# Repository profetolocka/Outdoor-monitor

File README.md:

[Go to English version](#english-version)

# Monitor ambiental de exterior

Consultá desde tu teléfono la temperatura, la humedad y la presión ambiental antes de salir de casa, con este práctico proyecto basado en un Atom Lite de M5Stack y la app ThingShow.

---

## 📂 Contenido

El repositorio está organizado en carpetas con el siguiente contenido:

**Code:** Código UIFlow2

**KiCad:** Proyecto de Kicad 9 con el esquemático y PCB

**images:** Imágenes para este archivo

---

## 📜 Funcionamiento

Lee la explicación completa del funcionamiento del monitor en mi blog:

[Monitorea el clima en tu teléfono con Atom Lite](https://www.profetolocka.com.ar/2025/06/30/monitorea-el-clima-en-tu-telefono-con-atom-lite/)

---

## 📜 Licencia

Este proyecto se publica bajo la licencia [MIT](LICENSE).

---

## ✍️ Autor

Creado por [Ernesto Tolocka](https://www.profetolocka.com.ar) – Profesor de electrónica, programación e IoT.

¡Encontrá más proyectos y tutoriales en el blog!

---

# Outdoor Environmental Monitor

Check the temperature, humidity, and atmospheric pressure from your phone before leaving home with this handy project based on an **M5Stack Atom Lite** and the **ThingShow** app.

---

## 📂 Contents

The repository is organized into folders with the following content:

**Code:** UIFlow2 code

**KiCad:** KiCad 9 project with schematic and PCB

**images:** Images for this file

---

## 📜 Operation

Read the full explanation of how the monitor works:

[Track outdoor weather on your phone using Atom Lite – PCBWay Project](https://www.pcbway.com/project/shareproject/Track_outdoor_weather_on_your_phone_using_Atom_Lite_3f8a86fd.html)

[Track outdoor weather on your phone using Atom Lite – Hackster.io](https://www.hackster.io/etolocka/track-outdoor-weather-on-your-phone-using-atom-lite-982a54)

---

## 📜 License

This project is published under the [MIT](LICENSE) license.

---

## ✍️ Author

Created by [Ernesto Tolocka](https://www.profetolocka.com.ar) – Electronics, programming, and IoT teacher.

Find more projects and tutorials on the blog!

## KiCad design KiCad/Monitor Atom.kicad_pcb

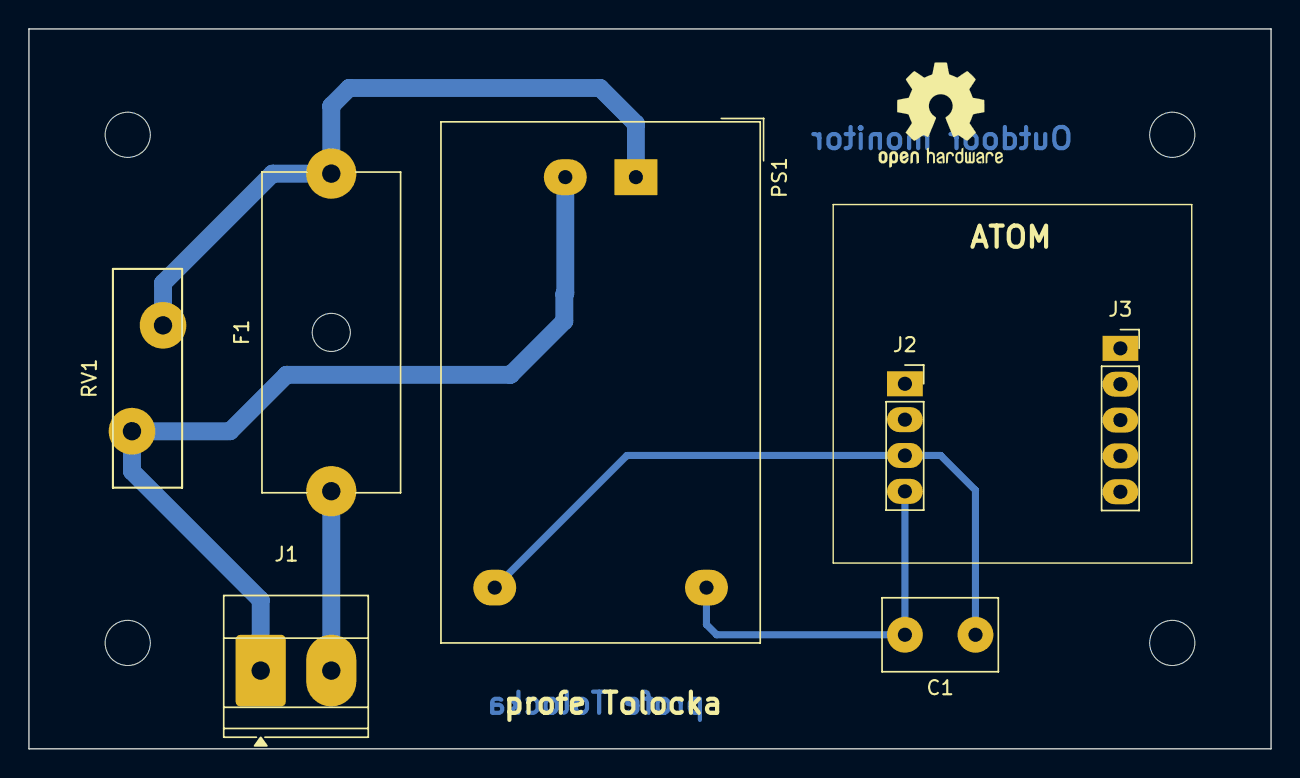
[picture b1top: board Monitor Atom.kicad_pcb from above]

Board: 2 copper layers, 88.0 x 51.0 mm, 7 parts (0 on the bottom side), 5 nets.

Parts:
C1: 0.1uF/35V; C_Disc_D8.0mm_W5.0mm_P5.00mm
F1: Fuse; Fuseholder_Cylinder-5x20mm_Schurter_0031_8201_Horizontal_Op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
J1: Screw_Terminal_01x02; TerminalBlock_Phoenix_MKDS-1,5-2_1x02_P5.00mm_Horizontal
J2: Conn_01x04; PinSocket_1x04_P2.54mm_Vertical
J3: Conn_01x05; PinSocket_1x05_P2.54mm_Vertical
PS1: TSP-05; Converter_ACDC_Hi-Link_HLK-PMxx
RV1: Varistor; RV_Disc_D15.5mm_W4.9mm_P7.5mm

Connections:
GNDREF: C1.2, J2.4, PS1.3 (-Vout)
unnamed: J1.1, PS1.2 (AC/N), RV1.2
unnamed: F1.1, J1.2
unnamed: C1.1, J2.3, PS1.4 (+Vout)
unnamed: F1.2, PS1.1 (AC/L), RV1.1

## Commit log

2025-08-09 Kicad files added
